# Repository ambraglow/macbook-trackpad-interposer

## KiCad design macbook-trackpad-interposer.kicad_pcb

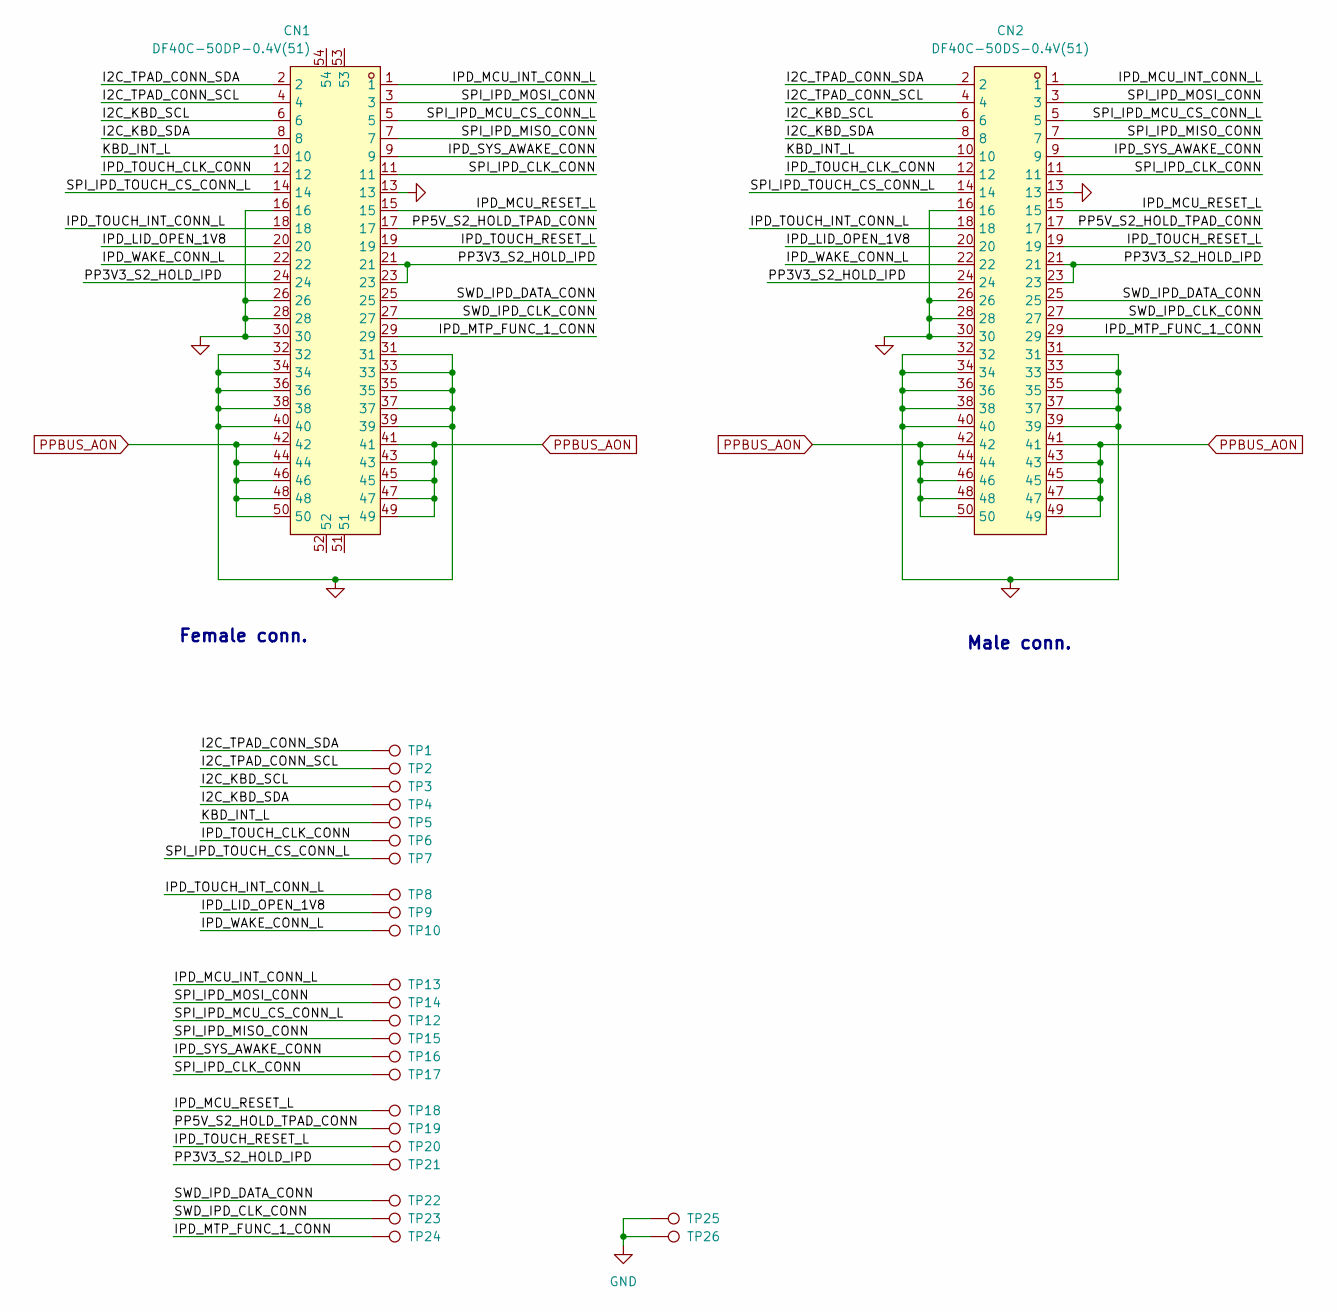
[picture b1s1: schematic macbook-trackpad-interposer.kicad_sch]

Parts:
CN1: DF40C-50DP-0.4V(51); CONN-SMD_DF40C-50DP-0.4V; LCSC Part C424645
CN2: DF40C-50DS-0.4V(51); CONN-SMD_DF40C-50DS-0.4V51; LCSC Part C424646
TP1, TP2, TP3, TP4, TP5, TP6, TP7, TP8, TP9, TP10, TP12, TP13, TP14, TP15, TP16, TP17, TP18, TP19, TP20, TP21, TP22, TP23, TP24, TP25, TP26: TestPoint; TestPoint_Pad_D1.5mm

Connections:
/I2C_KBD_SCL: CN1.6, CN2.6, TP3.1 (1_1)
/I2C_KBD_SDA: CN1.8, CN2.8, TP4.1 (1_1)
/I2C_TPAD_CONN_SCL: CN1.4, CN2.4, TP2.1 (1_1)
/I2C_TPAD_CONN_SDA: CN1.2, CN2.2, TP1.1 (1_1)
/IPD_LID_OPEN_1V8: CN1.20, CN2.20, TP9.1 (1_1)
/IPD_MCU_INT_CONN_L: CN1.1, CN2.1, TP13.1 (1_1)
/IPD_MCU_RESET_L: CN1.15, CN2.15, TP18.1 (1_1)
/IPD_MTP_FUNC_1_CONN: CN1.29, CN2.29, TP24.1 (1_1)
/IPD_SYS_AWAKE_CONN: CN1.9, CN2.9, TP16.1 (1_1)
/IPD_TOUCH_CLK_CONN: CN1.12, CN2.12, TP6.1 (1_1)
/IPD_TOUCH_INT_CONN_L: CN1.18, CN2.18, TP8.1 (1_1)
/IPD_TOUCH_RESET_L: CN1.19, CN2.19, TP20.1 (1_1)
/IPD_WAKE_CONN_L: CN1.22, CN2.22, TP10.1 (1_1)
/KBD_INT_L: CN1.10, CN2.10, TP5.1 (1_1)
/PP3V3_S2_HOLD_IPD: CN1.21, CN1.23, CN1.24, CN2.21, CN2.23, CN2.24, TP21.1 (1_1)
/PP5V_S2_HOLD_TPAD_CONN: CN1.17, CN2.17, TP19.1 (1_1)
/SPI_IPD_CLK_CONN: CN1.11, CN2.11, TP17.1 (1_1)
/SPI_IPD_MCU_CS_CONN_L: CN1.5, CN2.5, TP12.1 (1_1)
/SPI_IPD_MISO_CONN: CN1.7, CN2.7, TP15.1 (1_1)
/SPI_IPD_MOSI_CONN: CN1.3, CN2.3, TP14.1 (1_1)
/SPI_IPD_TOUCH_CS_CONN_L: CN1.14, CN2.14, TP7.1 (1_1)
/SWD_IPD_CLK_CONN: CN1.27, CN2.27, TP23.1 (1_1)
/SWD_IPD_DATA_CONN: CN1.25, CN2.25, TP22.1 (1_1)
GND: CN1.13, CN1.16, CN1.26, CN1.28, CN1.30, CN1.31, CN1.32, CN1.33, CN1.34, CN1.35, CN1.36, CN1.37, CN1.38, CN1.39, CN1.40, CN2.13, CN2.16, CN2.26, CN2.28, CN2.30, CN2.31, CN2.32, CN2.33, CN2.34, CN2.35, CN2.36, CN2.37, CN2.38, CN2.39, CN2.40, TP25.1 (1_1), TP26.1 (1_1)
PPBUS_AON: CN1.41, CN1.42, CN1.43, CN1.44, CN1.45, CN1.46, CN1.47, CN1.48, CN1.49, CN1.50, CN2.41, CN2.42, CN2.43, CN2.44, CN2.45, CN2.46, CN2.47, CN2.48, CN2.49, CN2.50

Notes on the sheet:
Female conn.
Male conn.

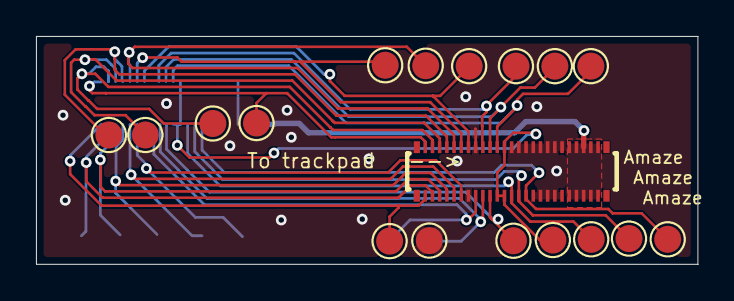
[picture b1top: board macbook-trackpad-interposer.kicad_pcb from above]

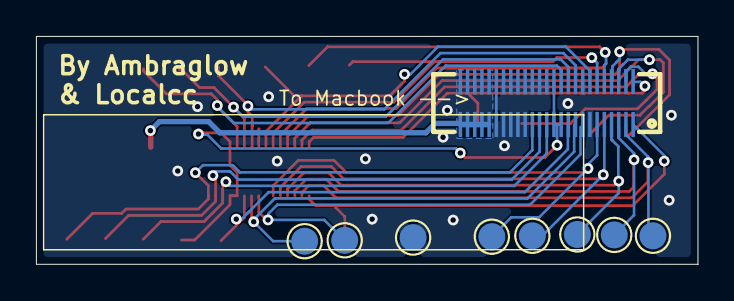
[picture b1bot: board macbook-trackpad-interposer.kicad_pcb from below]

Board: 2 copper layers, 36.8 x 12.7 mm, 27 parts (9 on the bottom side), 25 nets.

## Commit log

2026-03-28 Upload files
2026-03-28 remove .history
2026-04-01 unfuck the pcb
